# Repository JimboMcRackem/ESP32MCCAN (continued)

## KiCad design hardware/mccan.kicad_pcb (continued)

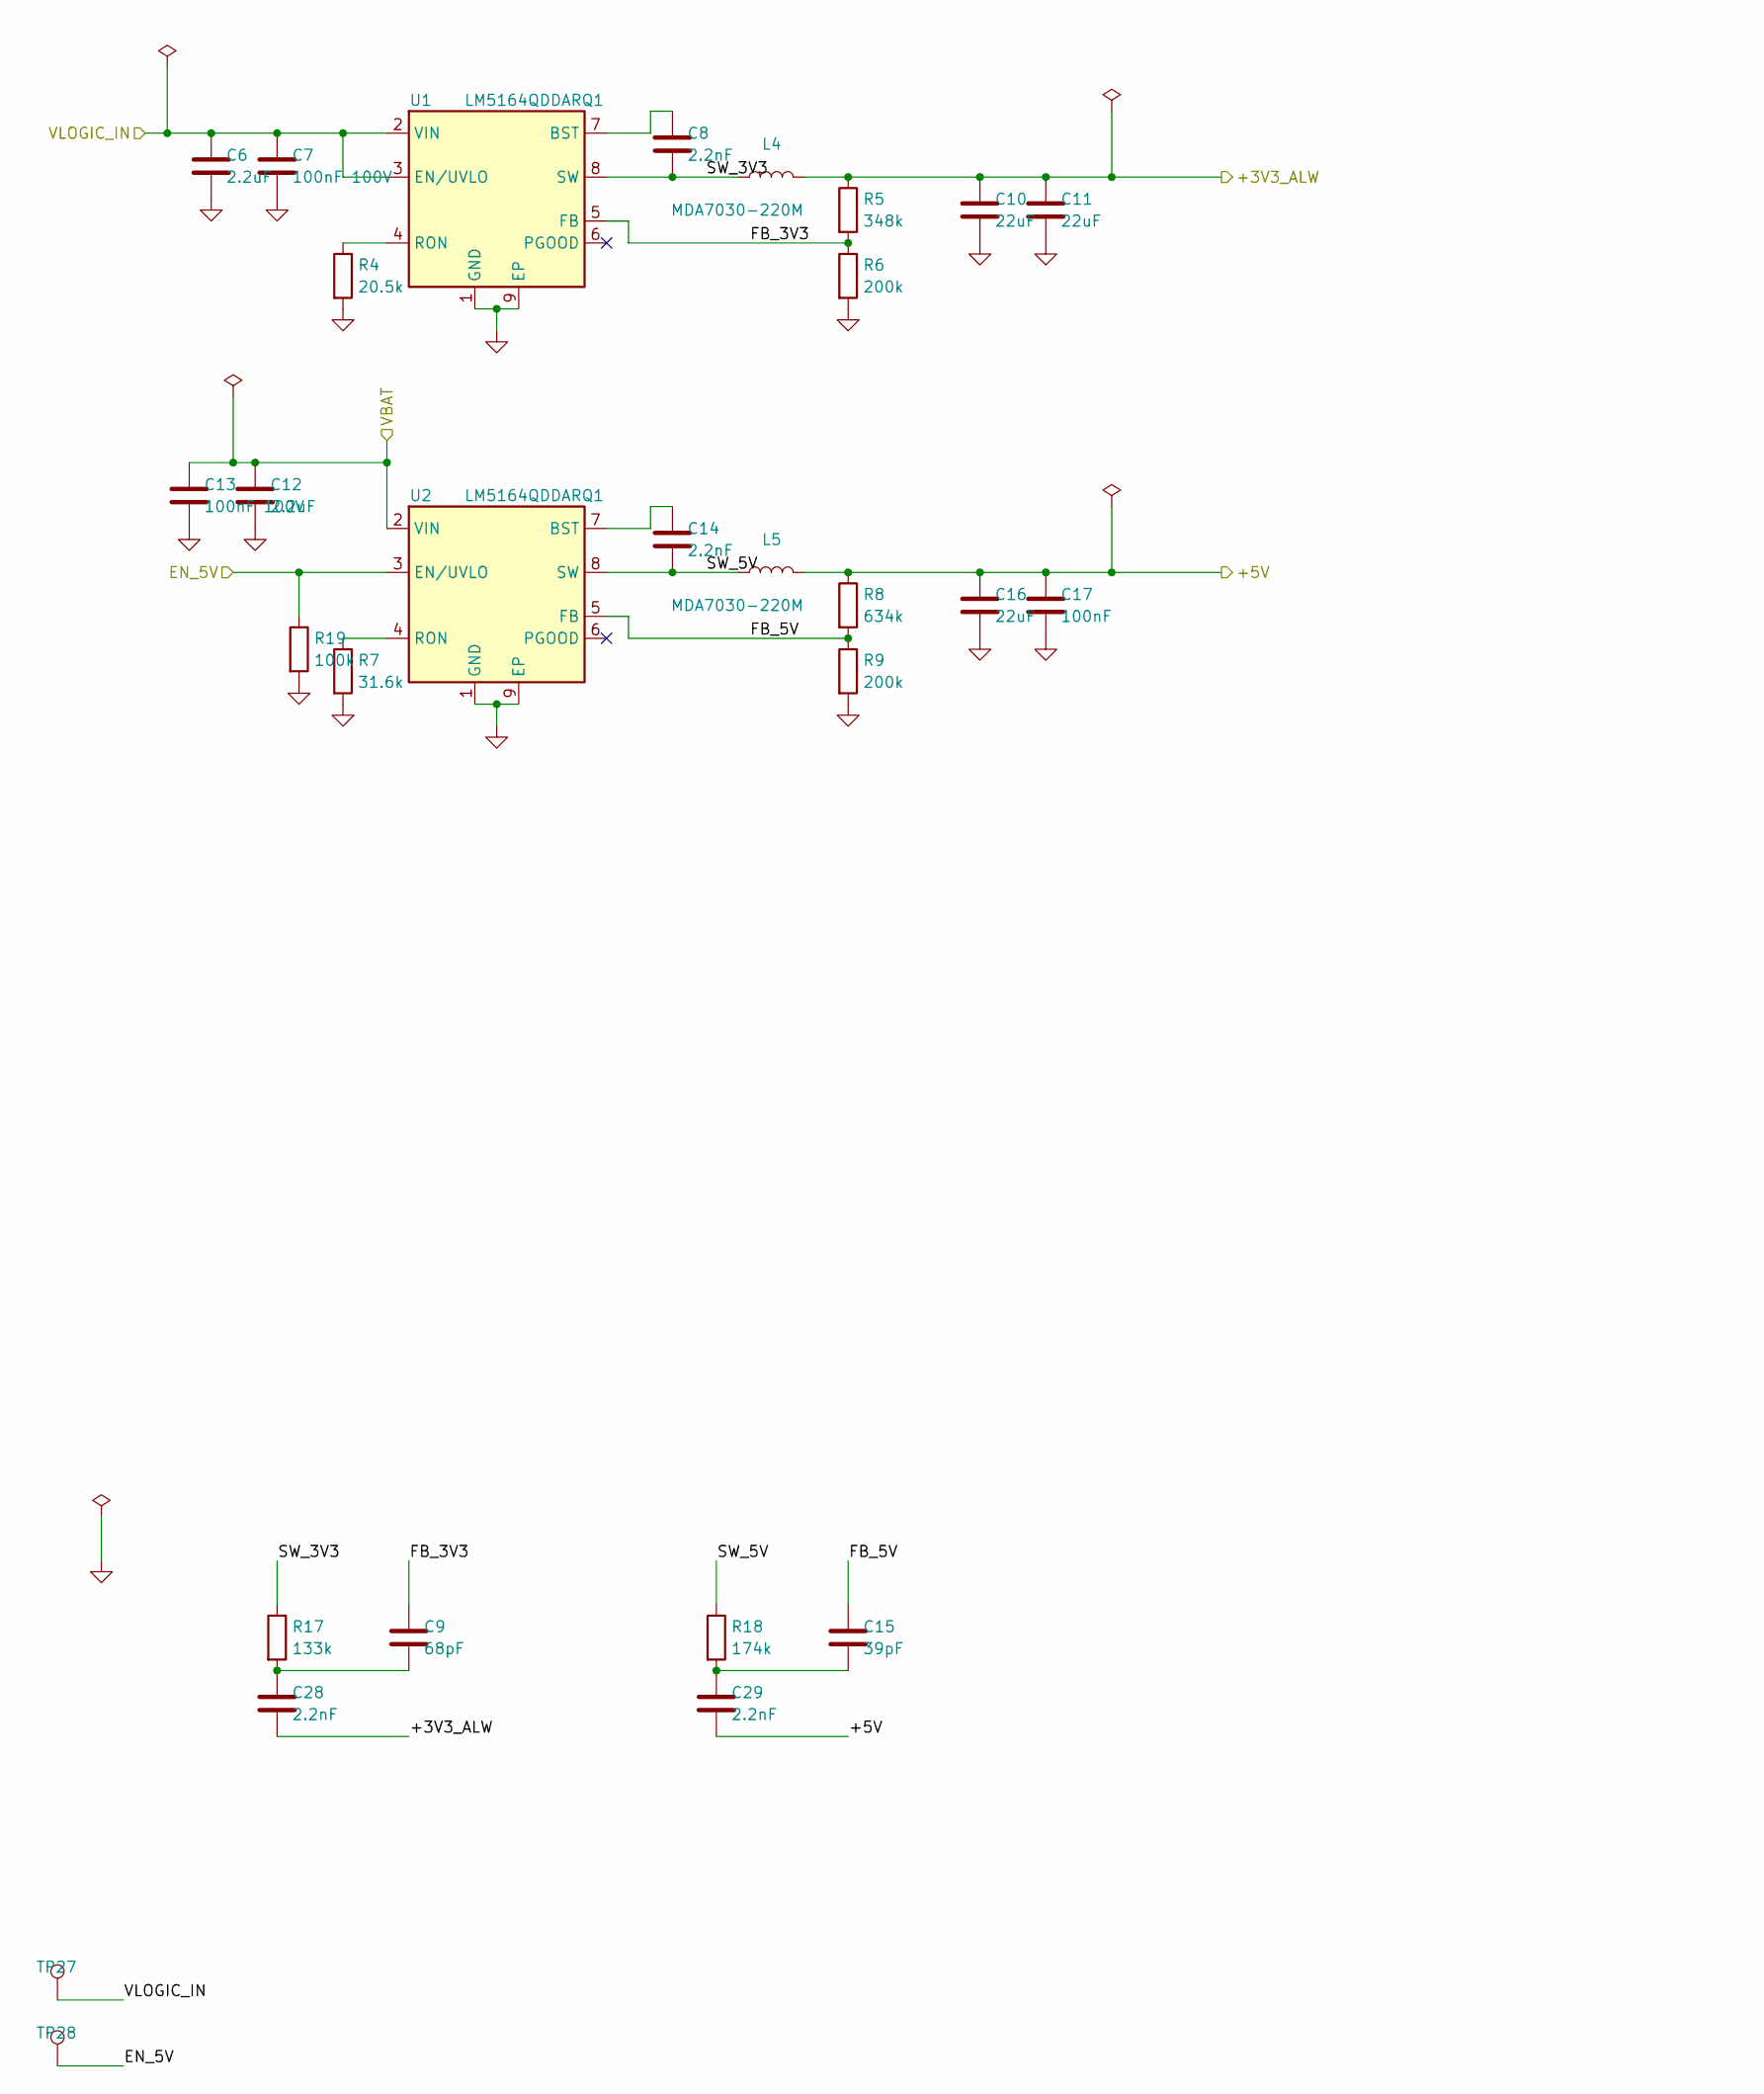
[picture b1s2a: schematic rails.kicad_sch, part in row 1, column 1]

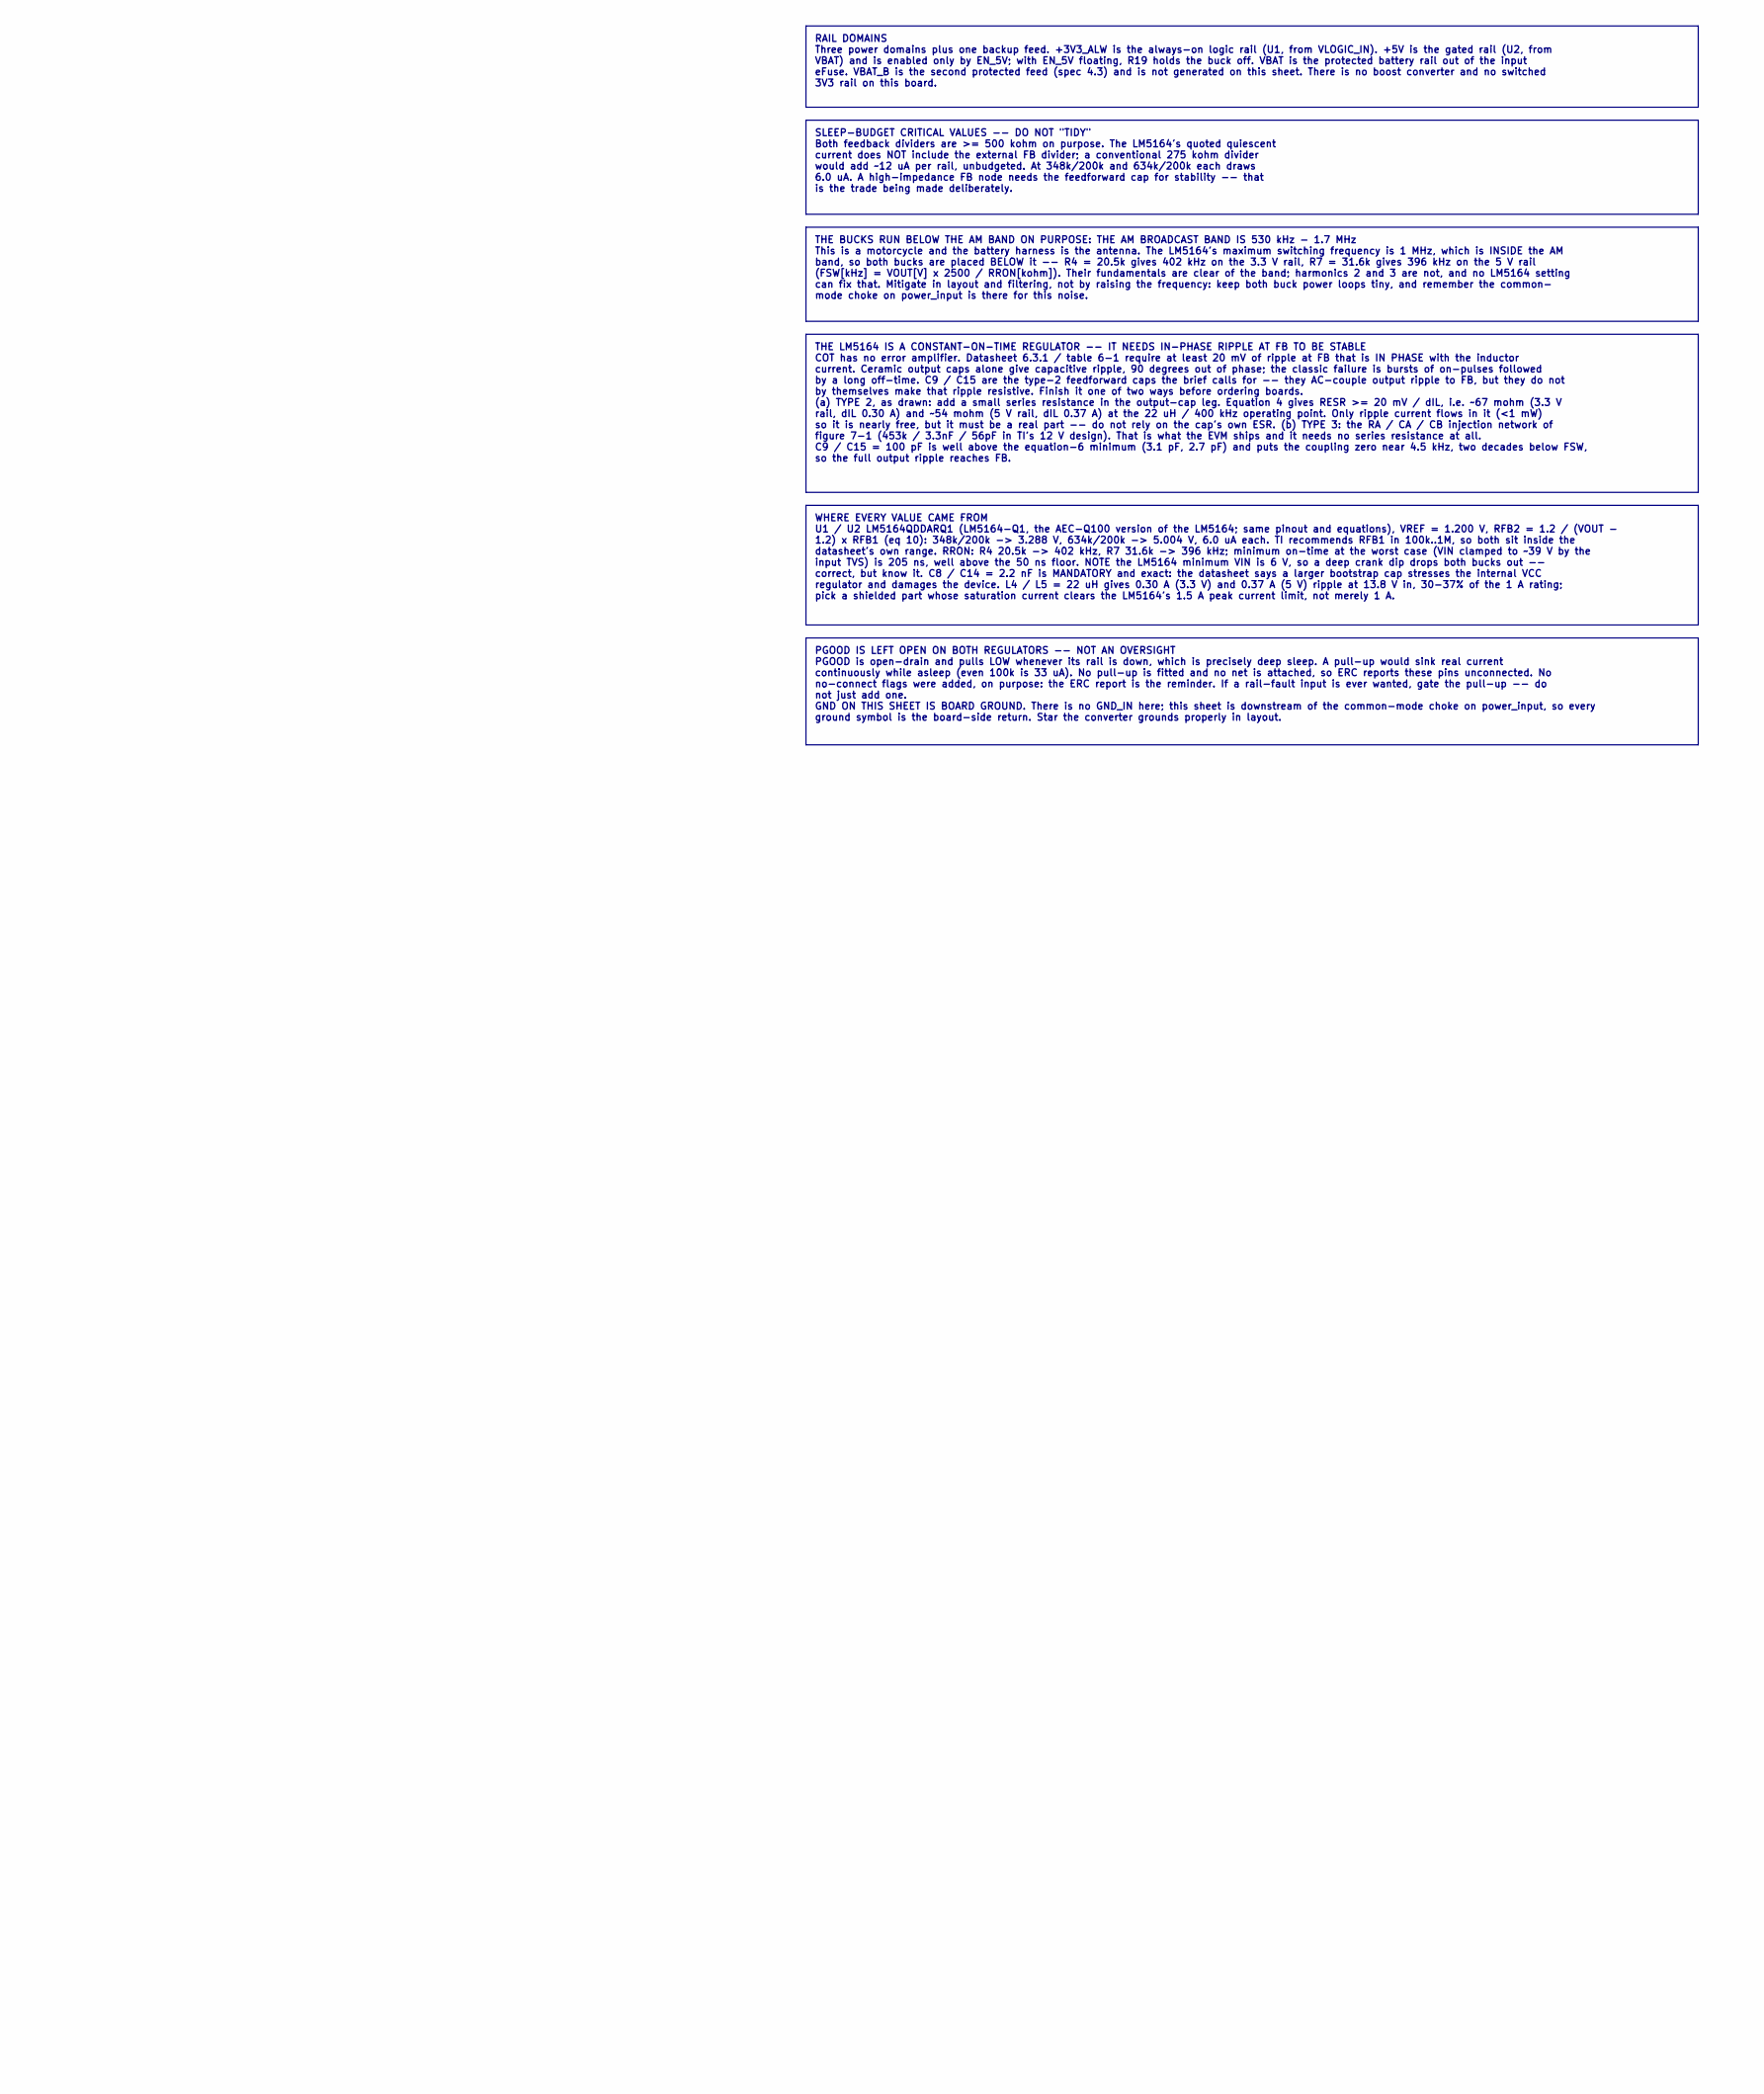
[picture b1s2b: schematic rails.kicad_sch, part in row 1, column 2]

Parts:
C6, C12: 2.2uF; C_1206_3216Metric
C7, C13: 100nF 100V; C_0805_2012Metric
C8, C14, C28, C29: 2.2nF; C_0603_1608Metric
C9: 68pF; C_0603_1608Metric
C10, C11, C16: 22uF; C_0603_1608Metric
C15: 39pF; C_0603_1608Metric
C17: 100nF; C_0603_1608Metric
L4, L5: MDA7030-220M; L_KOHERelec_MDA7030
R4: 20.5k; R_0603_1608Metric
R5: 348k; R_0603_1608Metric
R6, R9: 200k; R_0603_1608Metric
R7: 31.6k; R_0603_1608Metric
R8: 634k; R_0603_1608Metric
R17: 133k; R_0603_1608Metric
R18: 174k; R_0603_1608Metric
R19: 100k; R_0603_1608Metric
TP27: VLOGIC_IN; TestPoint_Pad_D1.5mm
TP28: EN_5V; TestPoint_Pad_D1.5mm
U1, U2: LM5164QDDARQ1; SOIC-8-1EP_3.9x4.9mm_P1.27mm_EP2.62x3.51mm

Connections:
/+3V3_ALW: C10.1, C11.1, C28.2, L4.2, R5.1; also elsewhere on the board
/+5V: C16.1, C17.1, C29.2, L5.2, R8.1; also elsewhere on the board
/EN_5V: R19.1, TP28.1, U2.3 (EN/UVLO); also elsewhere on the board
/VBAT: C12.1, C13.1, U2.2 (VIN); also elsewhere on the board
/VLOGIC_IN: C6.1, C7.1, TP27.1, U1.2 (VIN), U1.3 (EN/UVLO); also elsewhere on the board
/rails/FB_3V3: C9.1, R5.2, R6.1, U1.5 (FB)
/rails/FB_5V: C15.1, R8.2, R9.1, U2.5 (FB)
/rails/SW_3V3: C8.2, L4.1, R17.1, U1.8 (SW)
/rails/SW_5V: C14.2, L5.1, R18.1, U2.8 (SW)
GND: C6.2, C7.2, C10.2, C11.2, C12.2, C13.2, C16.2, C17.2, R4.2, R6.2, R7.2, R9.2, R19.2, U1.1 (GND), U1.9 (EP), U2.1 (GND), U2.9 (EP); also elsewhere on the board
unnamed: C15.2, C29.1, R18.2
unnamed: C9.2, C28.1, R17.2
unnamed: C8.1, U1.7 (BST)
unnamed: R4.1, U1.4 (RON)
unnamed: C14.1, U2.7 (BST)
unnamed: R7.1, U2.4 (RON)

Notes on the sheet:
THE LM5164 IS A CONSTANT-ON-TIME REGULATOR -- IT NEEDS IN-PHASE RIPPLE AT FB TO BE STABLE COT has no error amplifier. Datasheet 6.3.1 / table 6-1 require at least 20 mV of ripple at FB that is IN PHASE with the inductor current. Ceramic output caps alone give capacitive ripple, 90 degrees out of ph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
WHERE EVERY VALUE CAME FROM U1 / U2 LM5164QDDARQ1 (LM5164-Q1, the AEC-Q100 version of the LM5164; same pinout and equations), VREF = 1.200 V, RFB2 = 1.2 / (VOUT - 1.2) x RFB1 (eq 10): 348k/200k -> 3.288 V, 634k/200k -> 5.004 V, 6.0 uA each. TI recommends RFB1 in 100k..1M, so both sit inside the dat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
PGOOD IS LEFT OPEN ON BOTH REGULATORS -- NOT AN OVERSIGHT PGOOD is open-drain and pulls LOW whenever its rail is down, which is precisely deep sleep. A pull-up would sink real current continuously while asleep (even 100k is 33 uA). No pull-up is fitted and no net is attached, so ERC reports these p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
THE BUCKS RUN BELOW THE AM BAND ON PURPOSE: THE AM BROADCAST BAND IS 530 kHz - 1.7 MHz This is a motorcycle and the battery harness is the antenna. The LM5164's maximum switching frequency is 1 MHz, which is INSIDE the AM band, so both bucks are placed BELOW it -- R4 = 20.5k gives 402 kHz on the 3.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
RAIL DOMAINS Three power domains plus one backup feed. +3V3_ALW is the always-on logic rail (U1, from VLOGIC_IN). +5V is the gated rail (U2, from VBAT) and is enabled only by EN_5V; with EN_5V floating, R19 holds the buck off. VBAT is the protected battery rail out of the input eFuse. VBAT_B is the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
SLEEP-BUDGET CRITICAL VALUES -- DO NOT "TIDY" Both feedback dividers are >= 500 kohm on purpose. The LM5164's quoted quiescent current does NOT include the external FB divider; a conventional 275 kohm divider would add ~12 uA per rail, unbudgeted. At 348k/200k and 634k/200k each draws 6.0 uA. A hig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

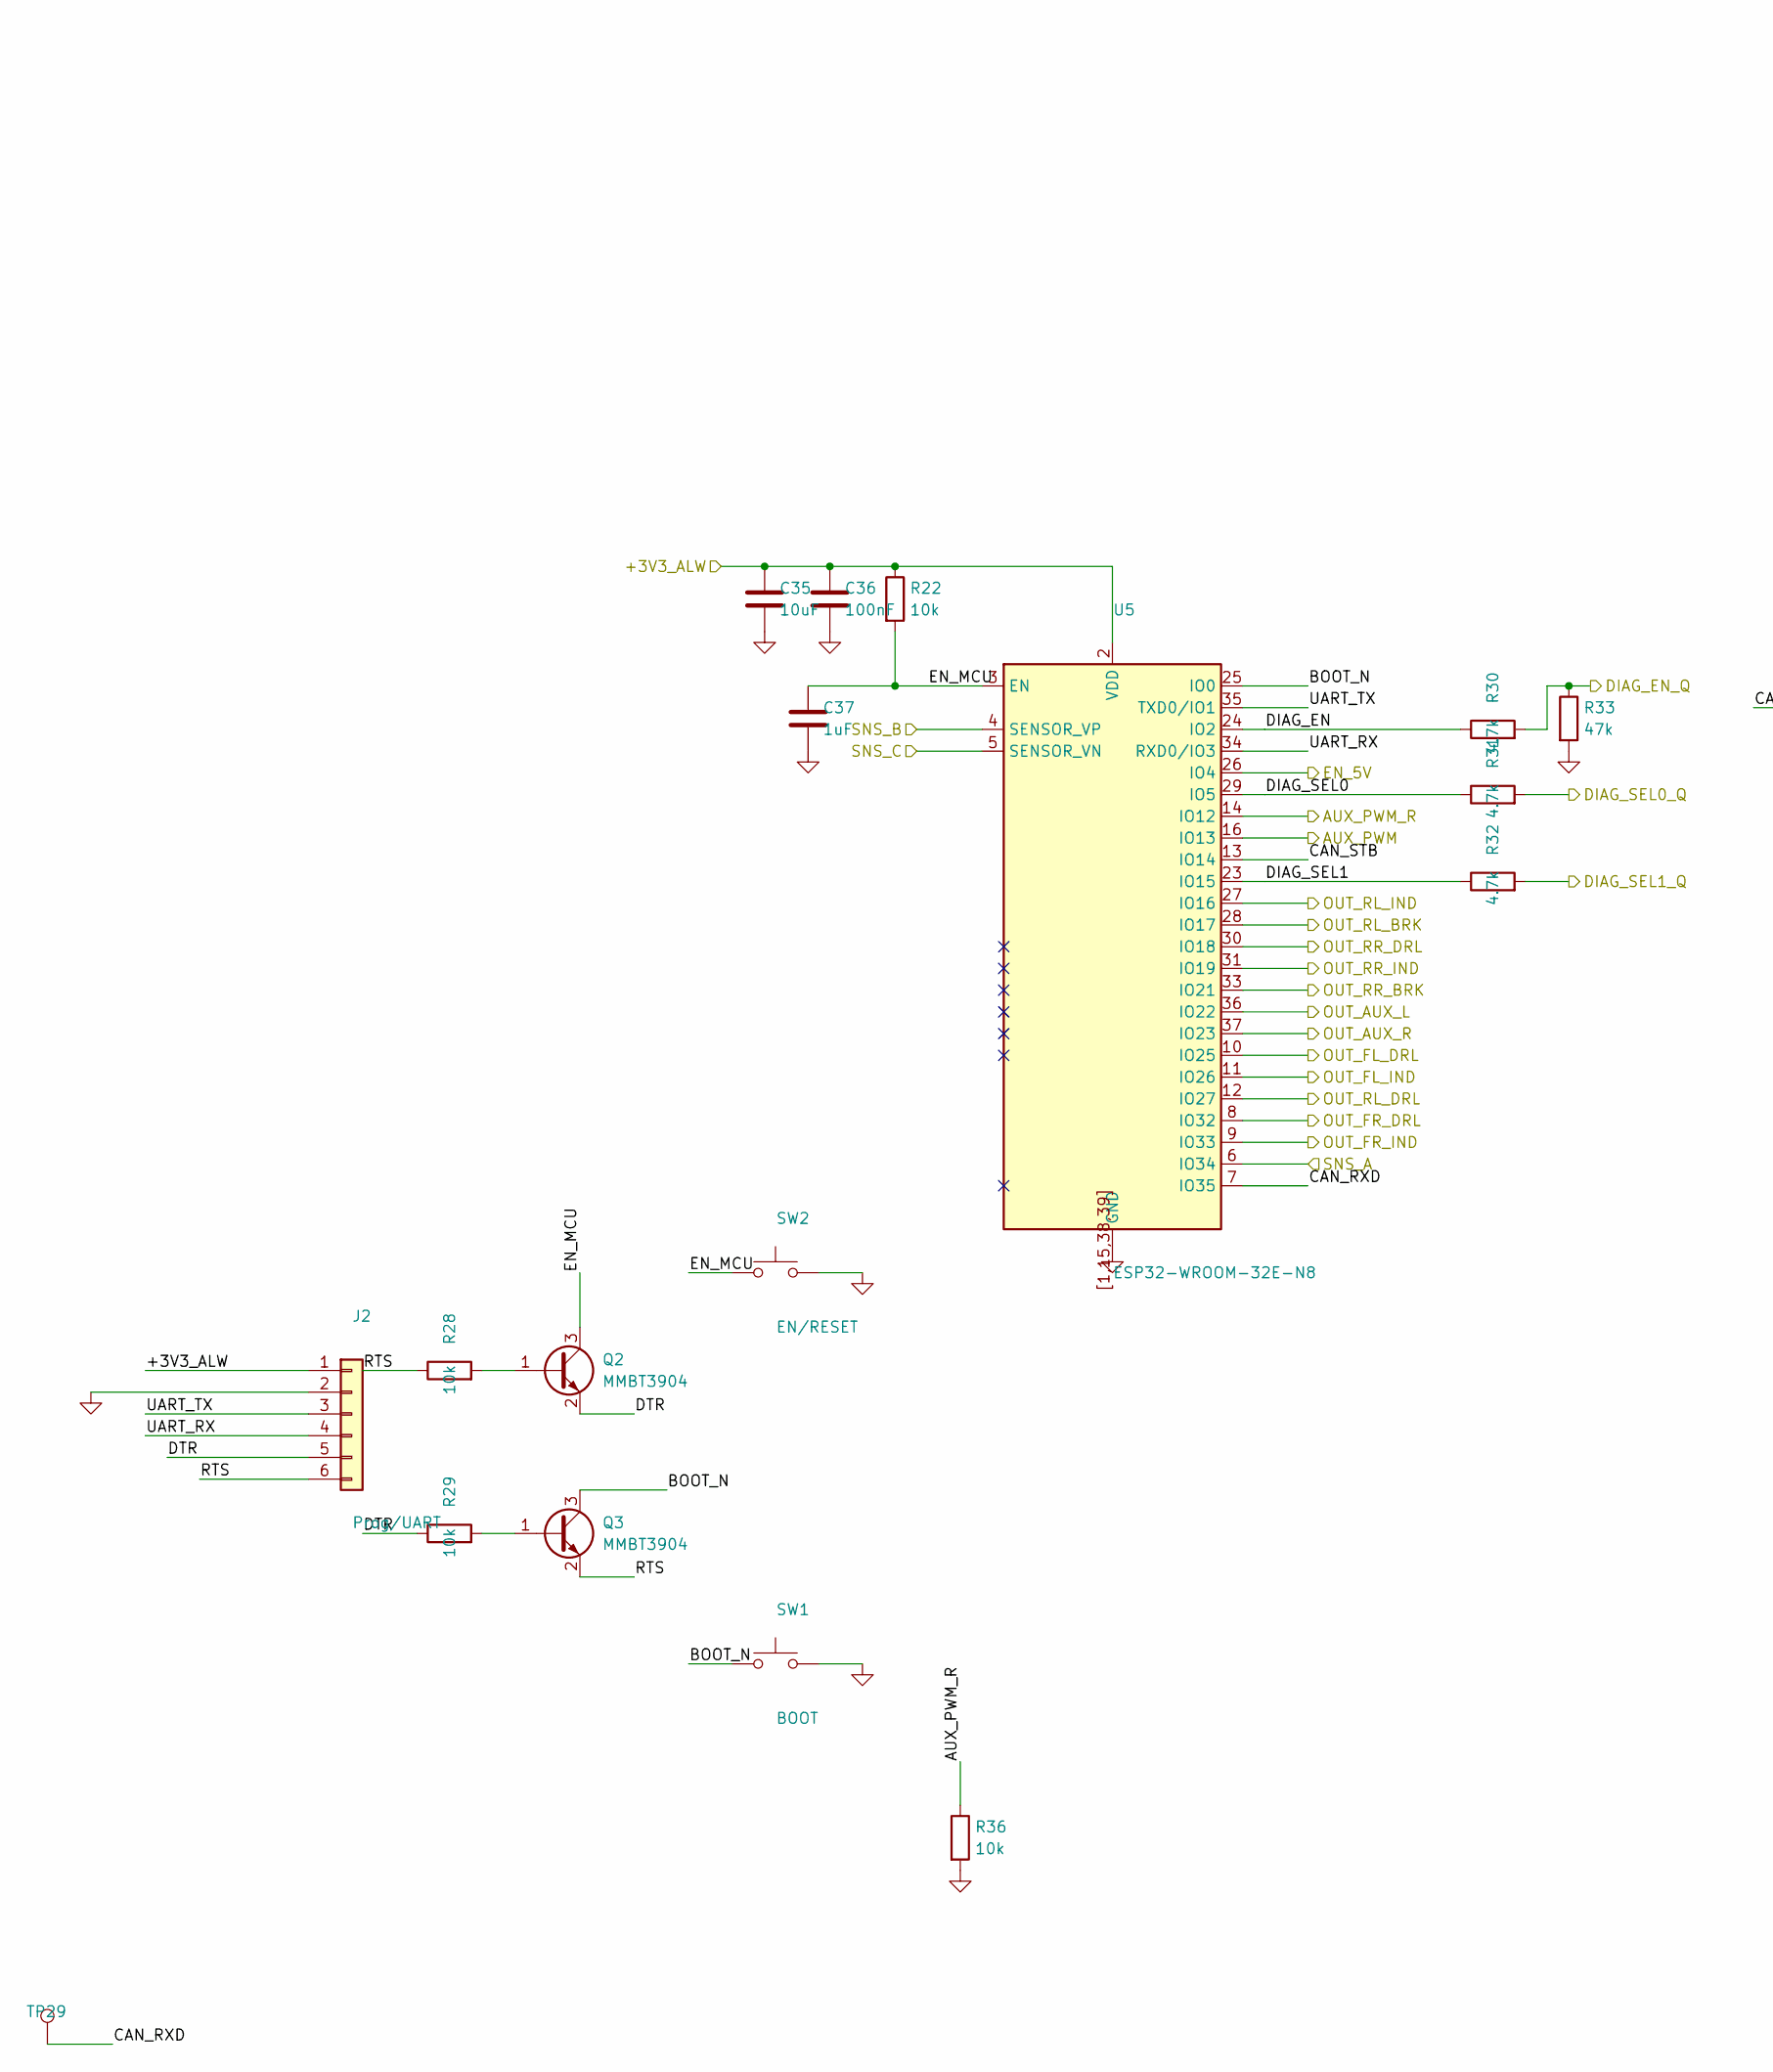
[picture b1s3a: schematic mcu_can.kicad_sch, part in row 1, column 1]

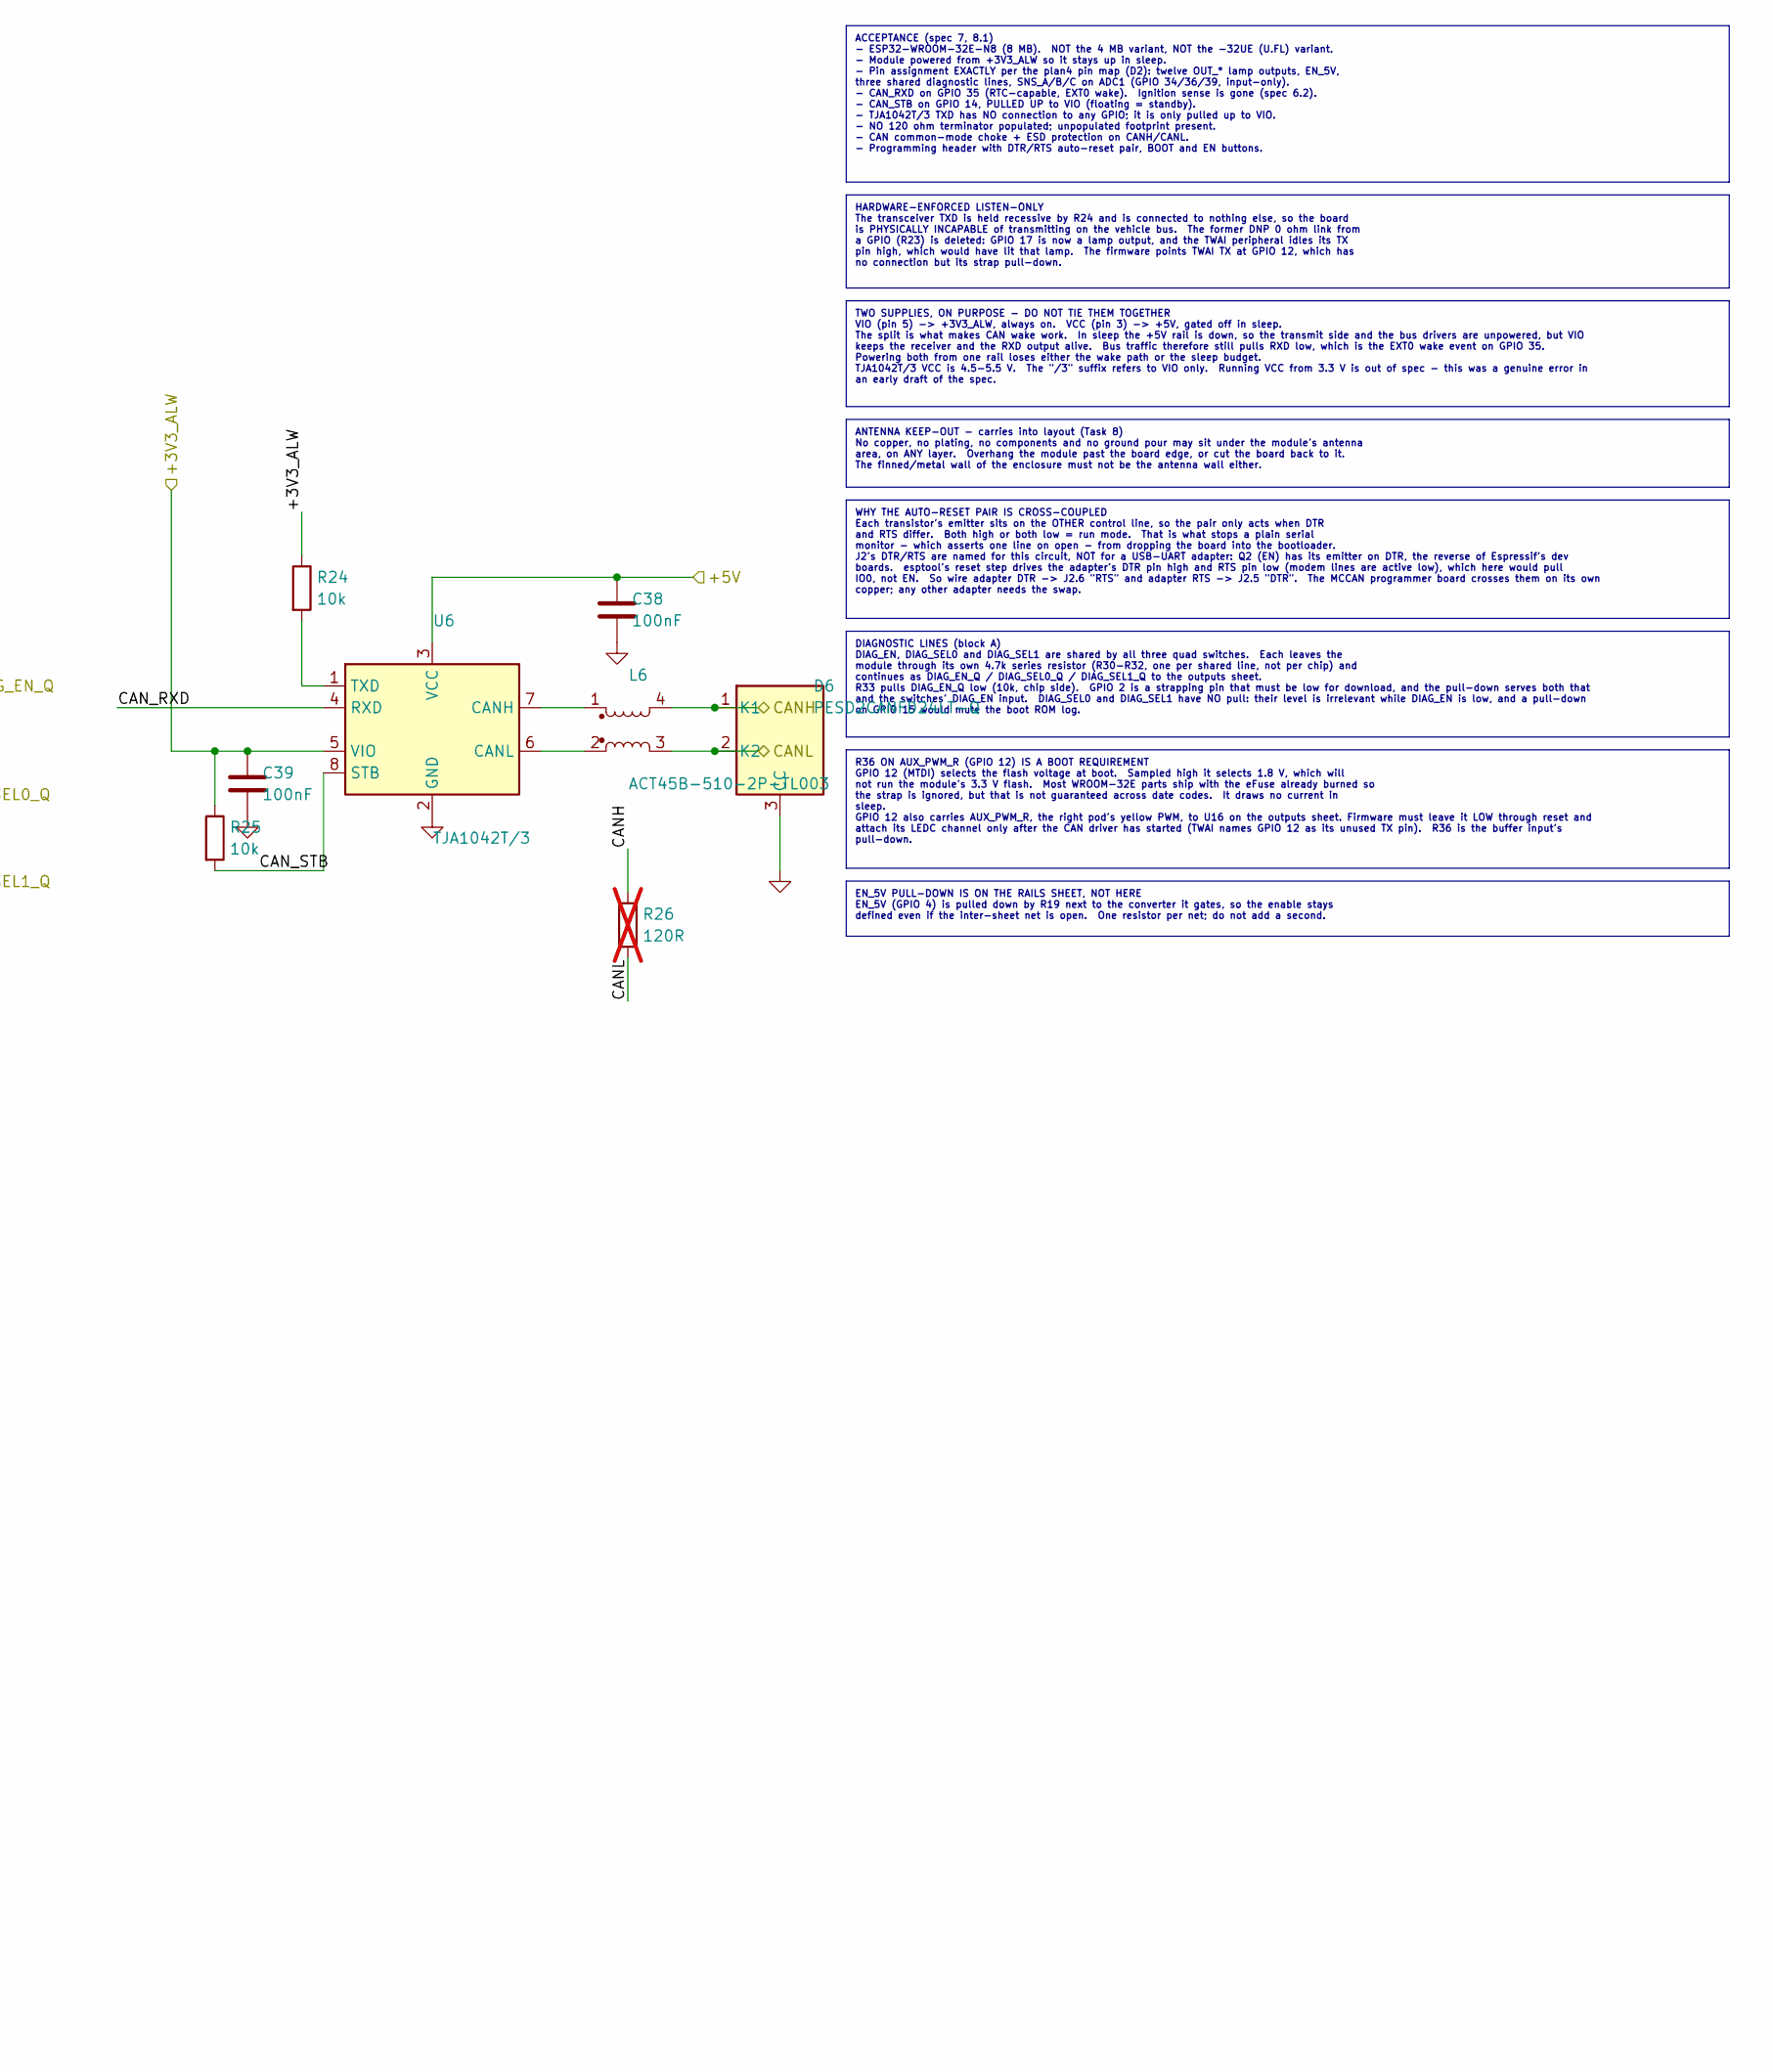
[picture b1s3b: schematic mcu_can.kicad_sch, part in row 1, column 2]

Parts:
C35: 10uF; C_0603_1608Metric
C36, C38, C39: 100nF; C_0603_1608Metric
C37: 1uF; C_0603_1608Metric
D6: PESD2CANFD24LT-Q; SOT-23
J2: Prog/UART; PinHeader_1x06_P2.54mm_Vertical
L6: ACT45B-510-2P-TL003; TDK_ACT45B
Q2, Q3: MMBT3904; SOT-23
R22, R24, R25, R28, R29, R36: 10k; R_0603_1608Metric
R26: 120R; R_0603_1608Metric; not fitted
R30, R31, R32: 4.7k; R_0603_1608Metric
R33: 47k; R_0603_1608Metric
SW1: BOOT; SW_Push_1P1T_XKB_TS-1187A
SW2: EN/RESET; SW_Push_1P1T_XKB_TS-1187A
TP29: CAN_RXD; TestPoint_Pad_D1.5mm
U5: ESP32-WROOM-32E-N8; ESP32-WROOM-32E
U6: TJA1042T/3; SOIC-8_3.9x4.9mm_P1.27mm

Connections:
/+3V3_ALW: C35.1, C36.1, C39.1, J2.1, R22.1, R24.1, R25.1, U5.2 (VDD), U6.5 (VIO); also elsewhere on the board
/+5V: C38.1, U6.3 (VCC); also elsewhere on the board
/AUX_PWM: U5.16 (IO13); also elsewhere on the board
/AUX_PWM_R: R36.1, U5.14 (IO12); also elsewhere on the board
/CANH: D6.1 (K1), L6.4, R26.1; also elsewhere on the board
/CANL: D6.2 (K2), L6.3, R26.2; also elsewhere on the board
/DIAG_EN_Q: R30.2, R33.1; also elsewhere on the board
/DIAG_SEL0_Q: R31.2; also elsewhere on the board
/DIAG_SEL1_Q: R32.2; also elsewhere on the board
/EN_5V: U5.26 (IO4); also elsewhere on the board
/OUT_AUX_L: U5.36 (IO22); also elsewhere on the board
/OUT_AUX_R: U5.37 (IO23); also elsewhere on the board
/OUT_FL_DRL: U5.10 (IO25); also elsewhere on the board
/OUT_FL_IND: U5.11 (IO26); also elsewhere on the board
/OUT_FR_DRL: U5.8 (IO32); also elsewhere on the board
/OUT_FR_IND: U5.9 (IO33); also elsewhere on the board
/OUT_RL_BRK: U5.28 (IO17); also elsewhere on the board
/OUT_RL_DRL: U5.12 (IO27); also elsewhere on the board
/OUT_RL_IND: U5.27 (IO16); also elsewhere on the board
/OUT_RR_BRK: U5.33 (IO21); also elsewhere on the board
/OUT_RR_DRL: U5.30 (IO18); also elsewhere on the board
/OUT_RR_IND: U5.31 (IO19); also elsewhere on the board
/SNS_A: U5.6 (IO34); also elsewhere on the board
/SNS_B: U5.4 (SENSOR_VP); also elsewhere on the board
/SNS_C: U5.5 (SENSOR_VN); also elsewhere on the board
/mcu_can/BOOT_N: Q3.3 (C), SW1.1, U5.25 (IO0)
/mcu_can/CAN_RXD: TP29.1, U5.7 (IO35), U6.4 (RXD)
/mcu_can/CAN_STB: R25.2, U5.13 (IO14), U6.8 (STB)
/mcu_can/DIAG_EN: R30.1, U5.24 (IO2)
/mcu_can/DIAG_SEL0: R31.1, U5.29 (IO5)
/mcu_can/DIAG_SEL1: R32.1, U5.23 (IO15)
/mcu_can/DTR: J2.5, Q2.2 (E), R29.1
/mcu_can/EN_MCU: C37.1, Q2.3 (C), R22.2, SW2.1, U5.3 (EN)
/mcu_can/RTS: J2.6, Q3.2 (E), R28.1
/mcu_can/UART_RX: J2.4, U5.34 (RXD0/IO3)
/mcu_can/UART_TX: J2.3, U5.35 (TXD0/IO1)
GND: C35.2, C36.2, C37.2, C38.2, C39.2, D6.3 (CC), J2.2, R33.2, R36.2, SW1.2, SW2.2, U5.1, U5.15, U5.38, U5.39, U5.[1,15,38,39] (GND), U6.2 (GND); also elsewhere on the board
unnamed: Q2.1 (B), R28.2
unnamed: Q3.1 (B), R29.2
unnamed: L6.1, U6.7 (CANH)
unnamed: L6.2, U6.6 (CANL)
unnamed: R24.2, U6.1 (TXD)

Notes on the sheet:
DIAGNOSTIC LINES (block A) DIAG_EN, DIAG_SEL0 and DIAG_SEL1 are shared by all three quad switches. Each leaves the module through its own 4.7k series resistor (R30-R32, one per shared line, not per chip) and continues as DIAG_EN_Q / DIAG_SEL0_Q / DIAG_SEL1_Q to the outputs sheet. R33 pulls DIAG_EN_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
WHY THE AUTO-RESET PAIR IS CROSS-COUPLED Each transistor's emitter sits on the OTHER control line, so the pair only acts when DTR and RTS differ. Both high or both low = run mode. That is what stops a plain serial monitor - which asserts one line on open - from dropping the board into the bootloade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
EN_5V PULL-DOWN IS ON THE RAILS SHEET, NOT HERE EN_5V (GPIO 4) is pulled down by R19 next to the converter it gates, so the enable stays defined even if the inter-sheet net is open. One resistor per net; do not add a second.
TWO SUPPLIES, ON PURPOSE - DO NOT TIE THEM TOGETHER VIO (pin 5) -> +3V3_ALW, always on. VCC (pin 3) -> +5V, gated off in sleep. The split is what makes CAN wake work. In sleep the +5V rail is down, so the transmit side and the bus drivers are unpowered, but VIO keeps the receiver and the RXD output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
HARDWARE-ENFORCED LISTEN-ONLY The transceiver TXD is held recessive by R24 and is connected to nothing else, so the board is PHYSICALLY INCAPABLE of transmitting on the vehicle bus. The former DNP 0 ohm link from a GPIO (R23) is deleted: GPIO 17 is now a lamp output, and the TWAI peripheral idles i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
R36 ON AUX_PWM_R (GPIO 12) IS A BOOT REQUIREMENT GPIO 12 (MTDI) selects the flash voltage at boot. Sampled high it selects 1.8 V, which will not run the module's 3.3 V flash. Most WROOM-32E parts ship with the eFuse already burned so the strap is ignored, but that is not guaranteed across date code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
ACCEPTANCE (spec 7, 8.1) - ESP32-WROOM-32E-N8 (8 MB). NOT the 4 MB variant, NOT the -32UE (U.FL) variant. - Module powered from +3V3_ALW so it stays up in sleep. - Pin assignment EXACTLY per the plan4 pin map (D2): twelve OUT_* lamp outputs, EN_5V, three shared diagnostic lines, SNS_A/B/C on ADC1 (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
ANTENNA KEEP-OUT - carries into layout (Task 8) No copper, no plating, no components and no ground pour may sit under the module's antenna area, on ANY layer. Overhang the module past the board edge, or cut the board back to it. The finned/metal wall of the enclosure must not be the antenna wall ei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
